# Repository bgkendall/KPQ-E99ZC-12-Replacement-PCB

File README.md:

# KPQ-E99ZC-12 Replacement PCB

## About

This is a replacement PCB for the [Mitsumi KPQ-E99ZC] keyboard of the mid-’90s. This new
PCB uses an STM32C071KBT6 or STM32G0B1KBT6 as the MCU. The pin-outs and behaviour of these
chips are the same and it should be possible to use either chip. The STM32C071 is cheaper,
but is currently (as of November 2025) unsupported by QMK and ZMK.

**CAUTION: Currently this PCB has not been produced and is untested.**

## Requirements

 * [KiCad] v9 or later
 * [BGKiCad library]

[Mitsumi KPQ-E99ZC]: https://web.archive.org/web/20240202015834/https://deskthority.net/wiki/Mitsumi_KPQ-E99ZC
[KiCad]: https://www.kicad.org
[BGKiCad library]: https://github.com/bgkendall/BGKiCad

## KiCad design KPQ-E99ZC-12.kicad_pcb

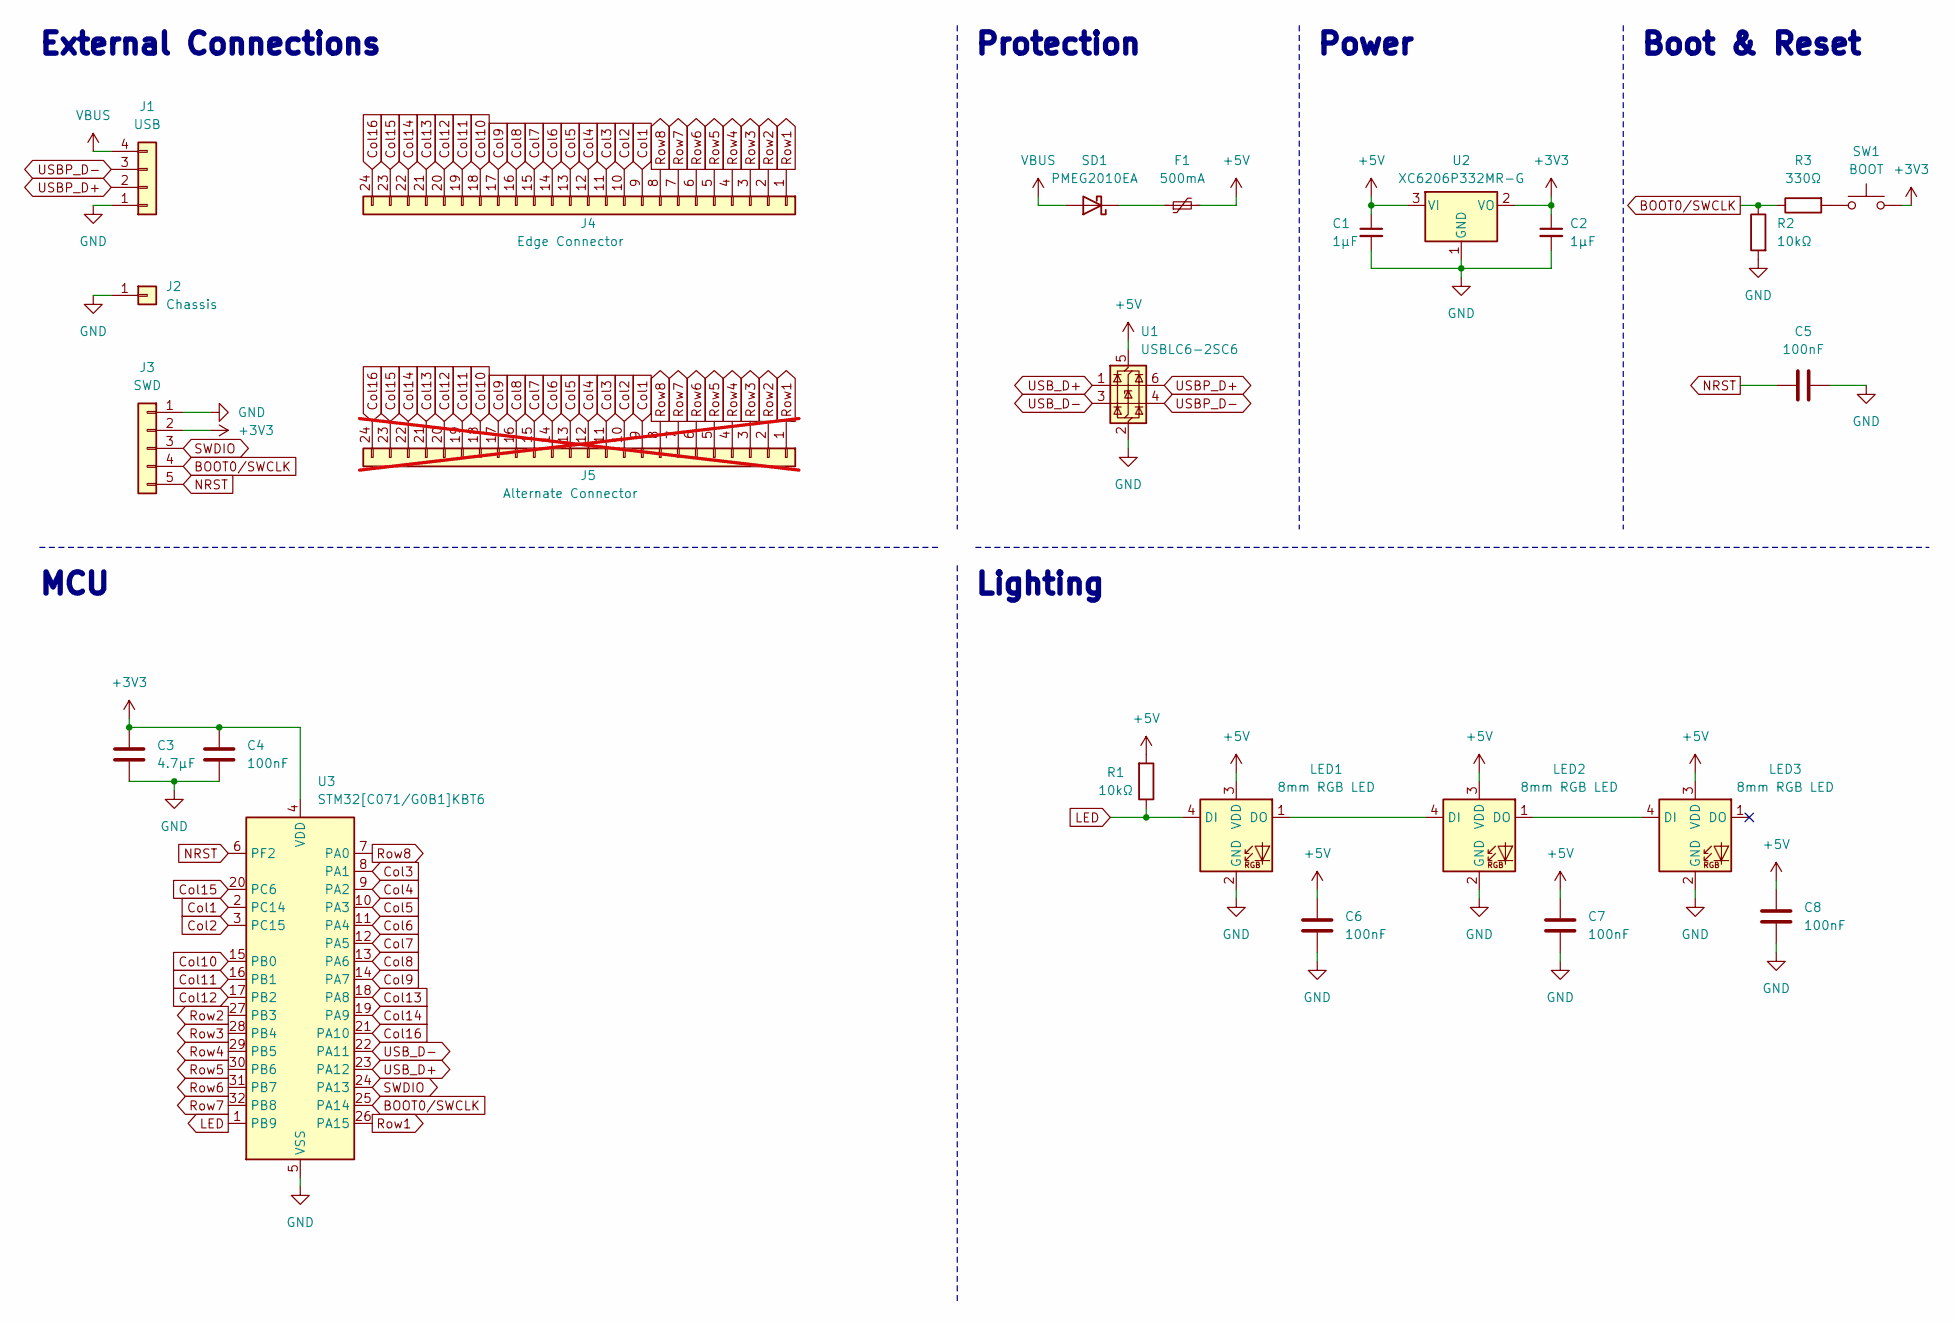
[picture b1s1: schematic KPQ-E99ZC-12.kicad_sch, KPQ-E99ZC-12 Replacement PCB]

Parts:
C1, C2: 1µF; C_0603_1608Metric; LCSC C52923
C3: 4.7µF; C_0603_1608Metric
C4, C5, C6, C7, C8: 100nF; C_0603_1608Metric
F1: 500mA; Fuse_0603_1608Metric_Pad1.05x0.95mm_HandSolder; LCSC C210357
J1: USB; PinHeader_1x04_P2.54mm_Vertical
J2: Chassis; SolderWire-0.5sqmm_1x01_D0.9mm_OD2.3mm
J3: SWD; PinHeader_1x05_P2.54mm_Vertical
J4: Edge Connector; Edge_Connector_01x24
J5: Alternate Connector; PinHeader_1x24_P2.54mm_Vertical; not fitted
LED1, LED2, LED3: 8mm RGB LED; LED_D5.0mm-4_RGB
R1, R2: 10kΩ; R_Combined_Axial_DIN0207_0603_1608Metric
R3: 330Ω; R_Combined_Axial_DIN0207_0603_1608Metric
SD1: PMEG2010EA; D_SOD-323_HandSoldering; LCSC C2837790
SW1: BOOT; SW_SPST_SKQG_WithStem; LCSC C231329
U1: USBLC6-2SC6; SOT-23-6
U2: XC6206P332MR-G; SOT-23-3
U3: STM32[C071/G0B1]KBT6; LQFP-32_7x7mm_P0.8mm

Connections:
+3V3: C2.1, C3.1, C4.1, J3.2, SW1.2, U2.2 (VO), U3.4 (VDD)
+5V: C1.1, C6.2, C7.2, C8.2, F1.2, LED1.3 (VDD), LED2.3 (VDD), LED3.3 (VDD), R1.2, U1.5 (VBUS), U2.3 (VI)
BOOT0/SWCLK: J3.4, R2.1, R3.1, U3.25 (PA14)
Col1: J4.9, J5.9, U3.2 (PC14)
Col2: J4.10, J5.10, U3.3 (PC15)
Col3: J4.11, J5.11, U3.8 (PA1)
Col4: J4.12, J5.12, U3.9 (PA2)
Col5: J4.13, J5.13, U3.10 (PA3)
Col6: J4.14, J5.14, U3.11 (PA4)
Col7: J4.15, J5.15, U3.12 (PA5)
Col8: J4.16, J5.16, U3.13 (PA6)
Col9: J4.17, J5.17, U3.14 (PA7)
Col10: J4.18, J5.18, U3.15 (PB0)
Col11: J4.19, J5.19, U3.16 (PB1)
Col12: J4.20, J5.20, U3.17 (PB2)
Col13: J4.21, J5.21, U3.18 (PA8)
Col14: J4.22, J5.22, U3.19 (PA9)
Col15: J4.23, J5.23, U3.20 (PC6)
Col16: J4.24, J5.24, U3.21 (PA10)
GND: C1.2, C2.2, C3.2, C4.2, C5.2, C6.1, C7.1, C8.1, J1.1, J2.1, J3.1, LED1.2 (GND), LED2.2 (GND), LED3.2 (GND), R2.2, U1.2 (GND), U2.1 (GND), U3.5 (VSS)
LED: LED1.4 (DI), R1.1, U3.1 (PB9)
NRST: C5.1, J3.5, U3.6 (PF2)
unnamed: LED1.1 (DO), LED2.4 (DI)
unnamed: LED2.1 (DO), LED3.4 (DI)
unnamed: R3.2, SW1.1
unnamed: F1.1, SD1.1 (K)
Row1: J4.1, J5.1, U3.26 (PA15)
Row2: J4.2, J5.2, U3.27 (PB3)
Row3: J4.3, J5.3, U3.28 (PB4)
Row4: J4.4, J5.4, U3.29 (PB5)
Row5: J4.5, J5.5, U3.30 (PB6)
Row6: J4.6, J5.6, U3.31 (PB7)
Row7: J4.7, J5.7, U3.32 (PB8)
Row8: J4.8, J5.8, U3.7 (PA0)
SWDIO: J3.3, U3.24 (PA13)
USBP_D+: J1.2, U1.6 (I/O1)
USBP_D-: J1.3, U1.4 (I/O2)
USB_D+: U1.1 (I/O1), U3.23 (PA12)
USB_D-: U1.3 (I/O2), U3.22 (PA11)
VBUS: J1.4, SD1.2 (A)

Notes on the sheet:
Boot & Reset
MCU
Power
Lighting
Protection
External Connections

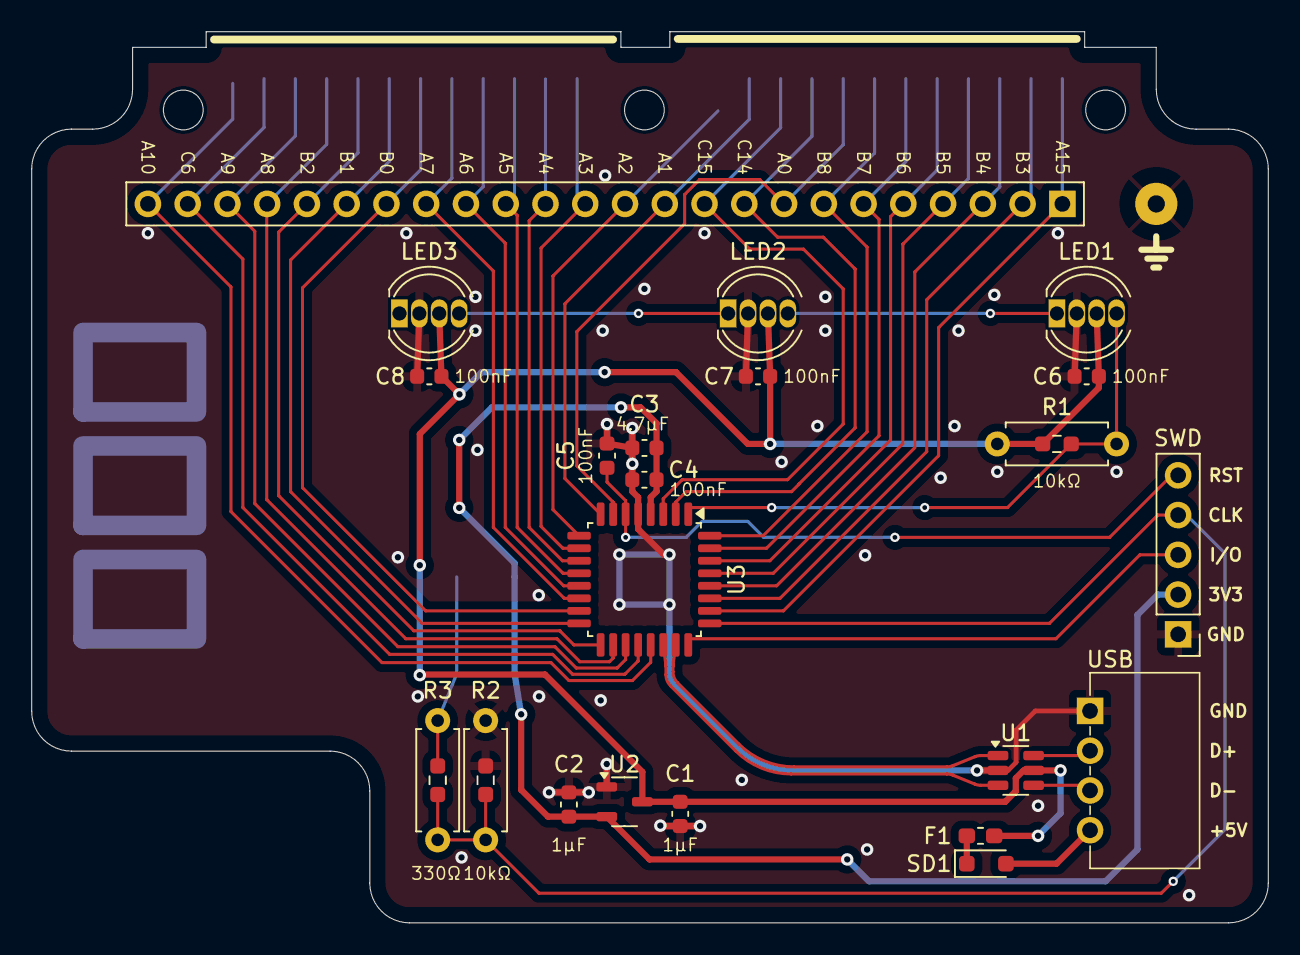
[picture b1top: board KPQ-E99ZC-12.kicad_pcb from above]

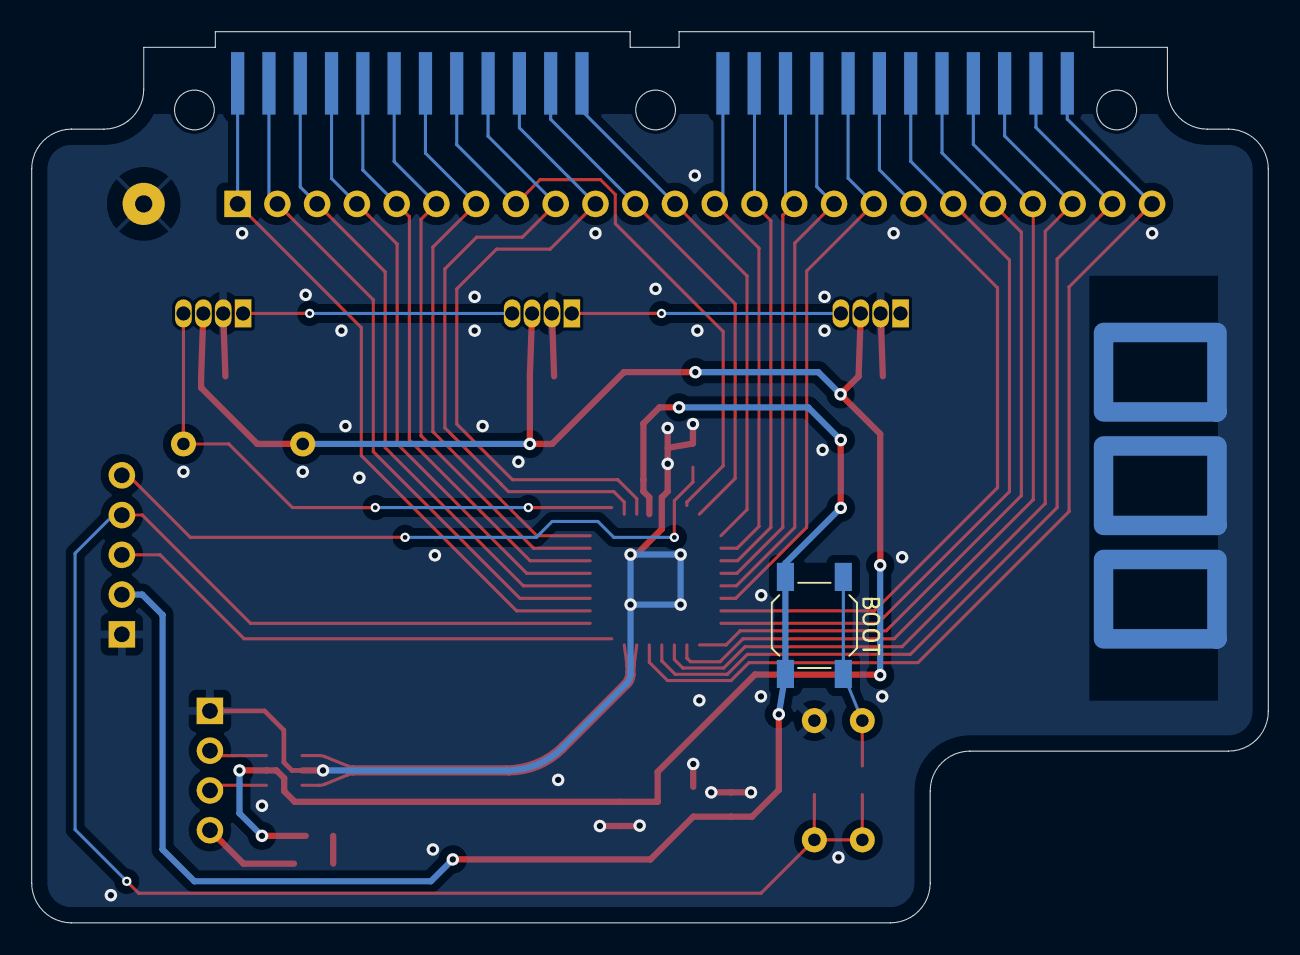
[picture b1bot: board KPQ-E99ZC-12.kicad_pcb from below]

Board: 2 copper layers, 79.0 x 56.9 mm, 25 parts (2 on the bottom side), 40 nets.

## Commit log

2025-03-03 Create LICENSE
2025-03-03 Add rough draft
2025-03-04 Update net classes
2025-03-04 Add measurements and tweak positions
2025-03-04 Swap LED pin
2025-03-06 Refine edges and positioning, especially around edge connectors
2025-03-11 Add +5V to SWD port, label SWD port, adjust PCB outline
    PCB outline and LED placement adjusted after comparing printout with actual PCB.
2025-03-11 Label USB post pins
2025-03-11 Remove pull-down resistor on BOOT0
    Since pin 25 is also a GPIO pin it has an internal pull-down resistor. The resistor is engaged on reset to allow for SWCLK functionality.
2025-03-11 Add board title, etc., to silkscreen
    Make “ミツミ” a de-boss in the rear copper layer.
2025-03-11 Tweak routing
2025-03-11 Fix DRC errors
2025-03-11 Flip boot switch to back
    This should be accessible through existing holes in the case near the tilt legs.
2025-03-11 Rotate LEDs
2025-03-11 Switch info text to DIN Alternate
2025-03-11 Tweak alignment of J1 and other minor adjustments
2025-03-11 Change R2 to R1 (since the previous R1 has been removed)
2025-03-11 Switch info. panel font to Alte DIN 1451 Mittelschrift
2025-03-13 Various tweaks, mostly to silkscreen
2025-03-13 Add copper and mask to back of edge connector
2025-03-13 Use correct symbol for RBG LEDs
    !!
2025-03-13 Tweak power routing
2025-03-13 Widen +5V routing under U1
2025-03-13 Remove +5V from J3
    This can be accessed via J1, and would avoid +5V being input from both J1 and J3 at the same time.
2025-03-13 Tweak “ミツミ” and info. panel
2025-03-15 Move BOOT switch over 1mm after testing with printout
    Plus some other minor tweaks
2025-03-16 Lock components that must not move
2025-03-16 Mark alternate connector as Do Not Populate
    This is mainly so that it can be filtered out of the 3D view!
2025-04-29 Minor tweaks
2025-05-10 Add additional ground vias and tweak routing
2025-05-31 Add pin labelling to alternate connection
2025-07-05 Round USB data lines; other routing tweaks
2025-10-20 Support STM32G0B1KBT6 in addition to STM32C071KBT6
    The pin-out is the same, but the G0B1 datasheet says that pin PC13, PC14 and PC15 should not be used as outputs. The schematic is therefore updated to move Row 8 away from PC14. This requires a littl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
2025-10-20 Update global label I/O directions
2025-10-20 Change R1 to combined THT/SMT footprint
2025-10-20 Add pin notes to schematic
2025-10-20 Tidied schematic
2025-11-16 Add boot resistor, tweak routing
2025-11-16 Add details to ReadMe
2025-11-16 Add values to resistors, tweak routing
2025-11-16 Remove DRC markers
2025-11-16 Update board render
2025-11-20 Update boot circuit, tweak positioning and routing
2025-11-20 Add PDF of schematic
2025-11-26 Updated via size, tweaked routing
2025-11-26 Added custom rule for 5mm RGB LEDs
2025-11-26 Add courtyards to edge connector
2025-12-23 Reroute 5V trace
2025-12-25 Minor routing tweak
